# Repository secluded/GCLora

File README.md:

# GCLora
An Arduino with a RFM95 Radio module capable of LoRa transmittions

Select "Lillypad Arduino USB" as the board type in the Arduino IDE
The GCLora board should automatically reconnect on another COM port for uploading code, 
then return to the orignal port on completion.
If this fails, double pressing the reset button will put it into upload mode, the led will pulse.

Pins RF Radio uses:<br>
MISO/MOSI/SCK (SPI)<br>
Version 1<br>
4(RST), 8(CS), A0(D0), 23(D1), A4(D2) is connectable by closing the jumper.<br>
Version 2 - enable use of Radiohead Library for non LoRaWan applications<br>
4(RST), 8(CS), 7(D0), 23(D1), A4(D2) is connectable by closing the jumper.<br>

For Australian use, please clone our Arduino/LMIC repo as it has the frequencies mapped correctly.

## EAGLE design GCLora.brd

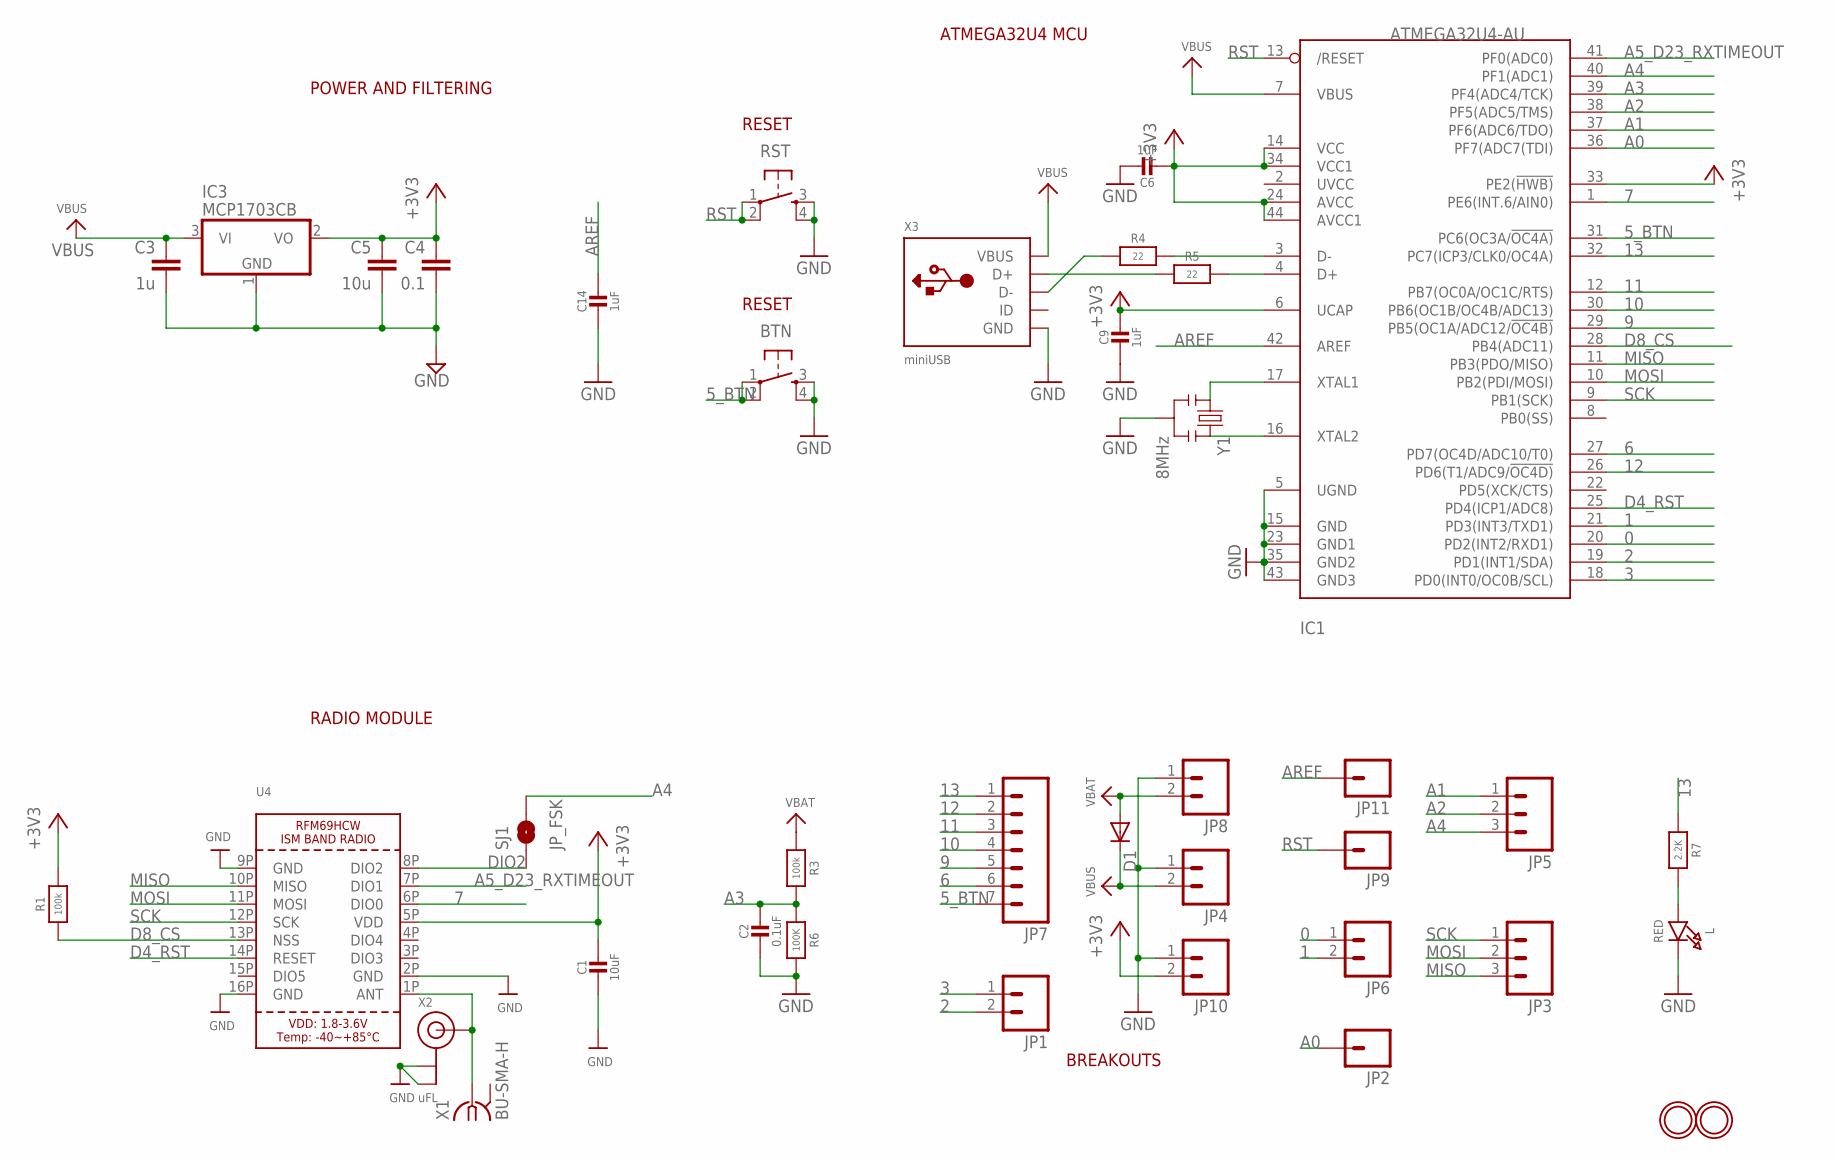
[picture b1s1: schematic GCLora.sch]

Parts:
BTN: TAC_SWITCHSMD; TACTILE_SWITCH_SMD
C1: 10uF; 0805-NO
C2: 0.1uF; 0805-NO
C3: 1u; 0805
C4: 0.1; 0805
C5: 10u; 0805-CAP
C6, C9, C14: 1uF; 0805-NO
D1: DIODESOD; SOD-323
IC1: ATMEGA32U4-AU; TQFP44
IC3: MCP1703CB; SOT23
JP1, JP4, JP6, JP8, JP10: M021X02_NO_SILK; 1X02_NO_SILK
JP2, JP9, JP11: M01PTH_NO_SILK_YES_STOP; 1X01_NO_SILK
JP3, JP5: M031X03_NO_SILK; 1X03_NO_SILK
JP7: M07; 1X07
L: RED; CHIPLED_0805_NOOUTLINE
R1, R3: 100k; 0805-NO
R4, R5: 22; 0805-NO
R6: 100K; 0805-NO
R7: 2.2K; 0805-NO
RST: TAC_SWITCHSMD; TACTILE_SWITCH_SMD
SJ1: JP_FSK; SPARKFUN-PASSIVES_SJ_2S-NO
U4: RFM69HCW_SMT; RFMHCW_SMT
U$31, U$32: MOUNTINGHOLE2.5; MOUNTINGHOLE_2.5_PLATED
X1: BU-SMA-H
X2: uFL; U.FL
X3: miniUSB; USB-MINIB_LARGER
Y1: 8MHz; RESONATOR-SMD

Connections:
0: IC1.20 (PD2(INT2/RXD1)), JP6.1
1: IC1.21 (PD3(INT3/TXD1)), JP6.2
2: IC1.19 (PD1(INT1/SDA)), JP1.2
3: IC1.18 (PD0(INT0/OC0B/SCL)), JP1.1
5_BTN: BTN.1, BTN.2, IC1.31 (PC6(OC3A/!OC4A)), JP7.7
6: IC1.27 (PD7(OC4D/ADC10/T0)), JP7.6
7: IC1.1 (PE6(INT.6/AIN0)), U4.6P (DIO0)
9: IC1.29 (PB5(OC1A/ADC12/!OC4B)), JP7.5
10: IC1.30 (PB6(OC1B/OC4B/ADC13)), JP7.4
11: IC1.12 (PB7(OC0A/OC1C/RTS)), JP7.3
12: IC1.26 (PD6(T1/ADC9/!OC4D)), JP7.2
13: IC1.32 (PC7(ICP3/CLK0/OC4A)), JP7.1, R7.1
+3V3: C1.1, C4.1, C5.1, C6.2, C9.1, IC1.6 (UCAP), IC1.14 (VCC), IC1.24 (AVCC), IC1.33 (PE2(!HWB)), IC1.34 (VCC1), IC1.44 (AVCC1), IC3.2 (VO), JP10.2, R1.2, U4.5P (VDD)
A0: IC1.36 (PF7(ADC7(TDI)), JP2.1
A1: IC1.37 (PF6(ADC6/TDO)), JP5.1
A2: IC1.38 (PF5(ADC5/TMS)), JP5.2
A3: C2.1, IC1.39 (PF4(ADC4/TCK)), R3.2, R6.1
A4: IC1.40 (PF1(ADC1)), JP5.3, SJ1.2
A5_D23_RXTIMEOUT: IC1.41 (PF0(ADC0)), U4.7P (DIO1)
ANT: U4.1P (ANT), X1.1, X2.3 (SIGNAL)
AREF: C14.1, IC1.42 (AREF), JP11.1
D4_RST: IC1.25 (PD4(ICP1/ADC8)), U4.14P (RESET)
D8_CS: IC1.28 (PB4(ADC11)), R1.1, U4.13P (NSS)
D+: IC1.4 (D+), R5.2
D-: IC1.3 (D-), R4.2
DIO2: SJ1.1, U4.8P (DIO2)
GND: BTN.3, BTN.4, C1.2, C2.2, C3.2, C4.2, C5.2, C6.1, C9.2, C14.2, IC1.5 (UGND), IC1.15 (GND), IC1.23 (GND1), IC1.35 (GND2), IC1.43 (GND3), IC3.1 (GND), JP4.1, JP8.1, JP10.1, L.C, R6.2, RST.3, RST.4, U4.2P (GND), U4.9P (GND), U4.16P (GND), X1.2 (GND), X1.3 (GND), X1.4 (GND), X1.5 (GND), X2.1 (GND), X2.2 (GND), X3.GND, X3.GND1 (GND), X3.GND2 (GND), X3.GND3 (GND), X3.GND4 (GND), Y1.2
MISO: IC1.11 (PB3(PDO/MISO)), JP3.3, U4.10P (MISO)
MOSI: IC1.10 (PB2(PDI/MOSI)), JP3.2, U4.11P (MOSI)
unnamed: L.A, R7.2
unnamed: IC1.16 (XTAL2), Y1.3
unnamed: IC1.17 (XTAL1), Y1.1
unnamed: R5.1, X3.D+
unnamed: R4.1, X3.D-
RST: IC1.13 (/RESET), JP9.1, RST.1, RST.2
SCK: IC1.9 (PB1(SCK)), JP3.1, U4.12P (SCK)
VBAT: D1.2 (A), JP8.2, R3.1
VBUS: C3.1, D1.1 (C), IC1.7 (VBUS), IC3.3 (VI), JP4.2, X3.VBUS

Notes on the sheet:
POWER AND FILTERING
RESET
ATMEGA32U4 MCU
BREAKOUTS
RADIO MODULE

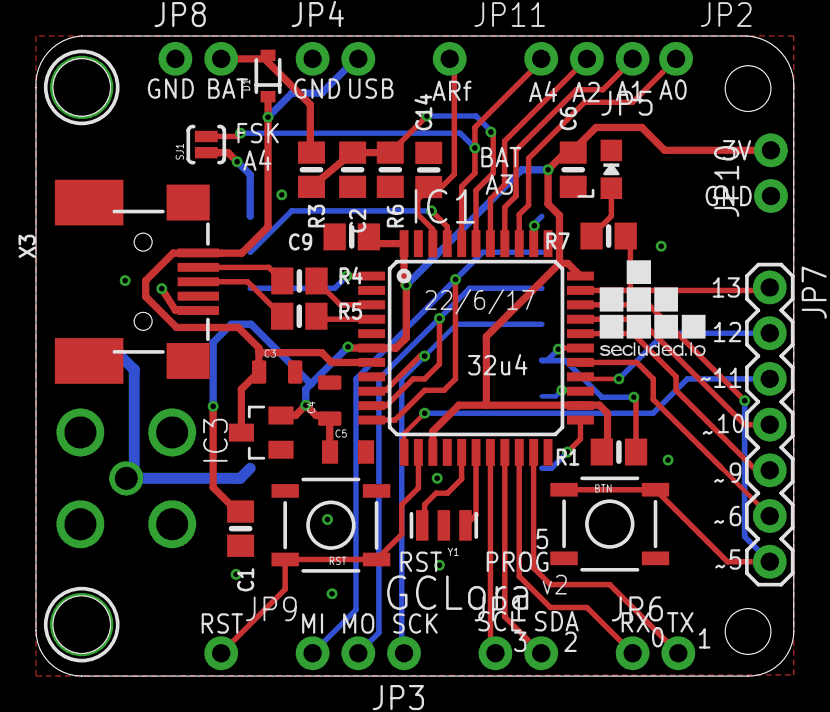
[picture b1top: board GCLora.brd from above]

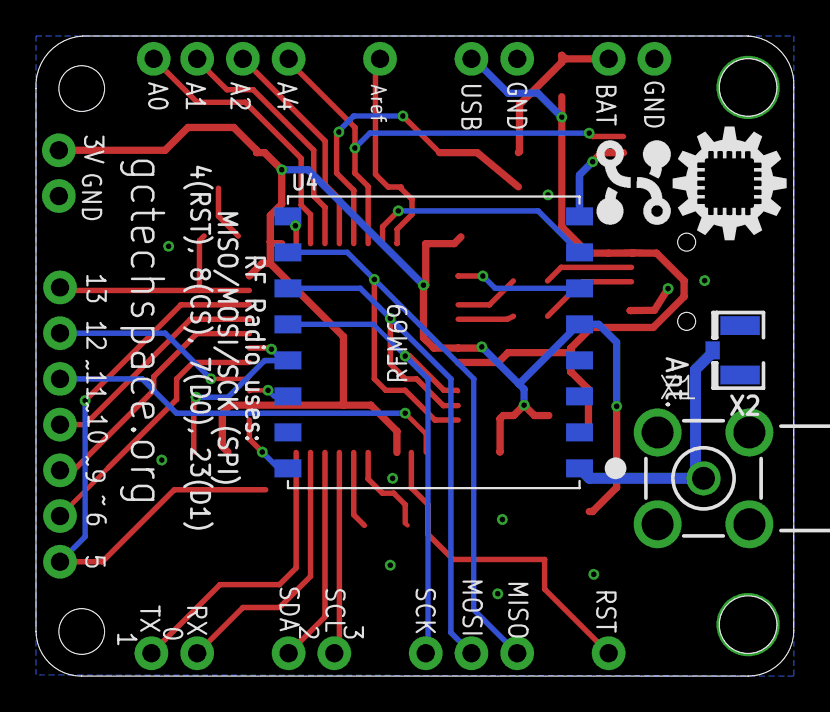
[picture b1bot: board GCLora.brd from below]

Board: 2 copper layers, 42.1 x 35.6 mm, 42 parts (5 on the bottom side), 38 nets.

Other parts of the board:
U$6: ESPDUINO_LOGO_5MM
U$7: SECLUDED_5MM
U$15: ID_LOGO_X0.25

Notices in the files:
parts and their libraries:
microbuilder: This work is placed in the public domain, and may be freely used for commercial and non-commercial work with the following conditions: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
SparkFun: Licensing: CC v3.0 Share-Alike You are welcome to use this library for commercial purposes.
